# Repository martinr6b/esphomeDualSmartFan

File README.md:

# Pcb for reading rpm and adjusting speed of two 4-pin pwm capable fans
[)](https://discord.gg/c2CaMQDF9t)

## the board itself
⚠️I HAVE NOT ORDERED THE BOARD YET SO THE GERBERS COULD BE BROKEN⚠️
- designed in kicad
- risky gerbers available
- based around ESP32-WROOM-32U
- powered by barrel jack in combination with a LM1117DT-3.3 voltage regulator

### BOM list
TODO
## Code
TODO

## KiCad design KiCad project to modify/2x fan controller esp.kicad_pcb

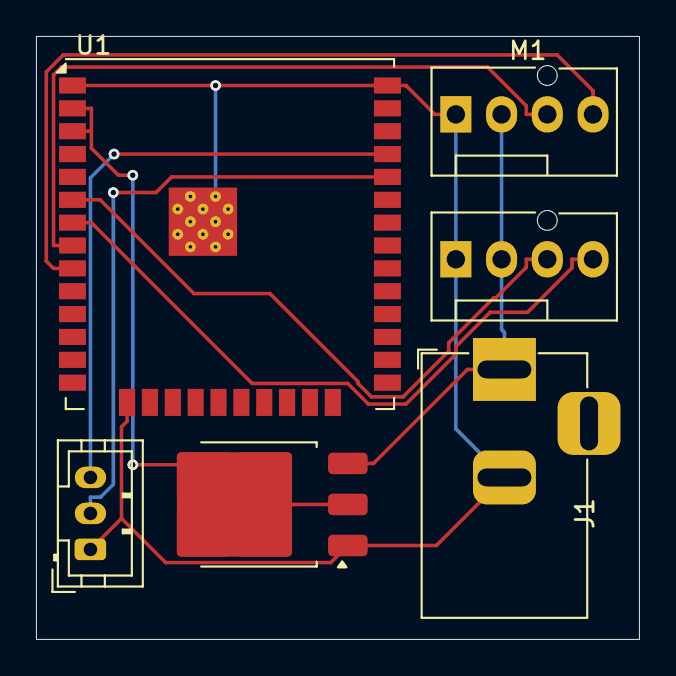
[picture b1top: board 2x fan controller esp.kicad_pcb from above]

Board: 2 copper layers, 33.5 x 33.5 mm, 6 parts (0 on the bottom side), 9 nets.

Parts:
J1: Barrel_Jack_MountingPin; BarrelJack_Horizontal
J2: Conn_01x03_Pin; JST_PH_B3B-PH-K_1x03_P2.00mm_Vertical
M1, M2: Fan_4pin; FanPinHeader_1x04_P2.54mm_Vertical
U1: ESP32-WROOM-32U
U2: LM1117DT-3.3; TO-252-3_TabPin2

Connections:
unnamed: J1.2, J2.1, M1.1 (-), M2.1 (-), U1.1 (GND), U1.15 (GND), U1.38 (GND), U1.39 (GND), U2.1 (GND)
unnamed: J2.2, U1.34 (RXD0/IO3)
unnamed: J2.3, U1.35 (TXD0/IO1)
unnamed: J1.1, M1.2 (+), M2.2 (+), U2.3 (VI)
unnamed: M1.4 (PWM), U1.9 (IO33)
unnamed: M1.3 (Tacho), U1.8 (IO32)
unnamed: M2.4 (PWM), U1.7 (IO35)
unnamed: M2.3 (Tacho), U1.6 (IO34)
unnamed: U1.2 (VDD), U1.3 (EN), U2.2 (VO)

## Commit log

2025-03-03 uploaded files
    added gerbers and kicad project folder
